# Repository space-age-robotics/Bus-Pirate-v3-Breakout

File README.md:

Bus-Pirate-v3-Breakout
======================

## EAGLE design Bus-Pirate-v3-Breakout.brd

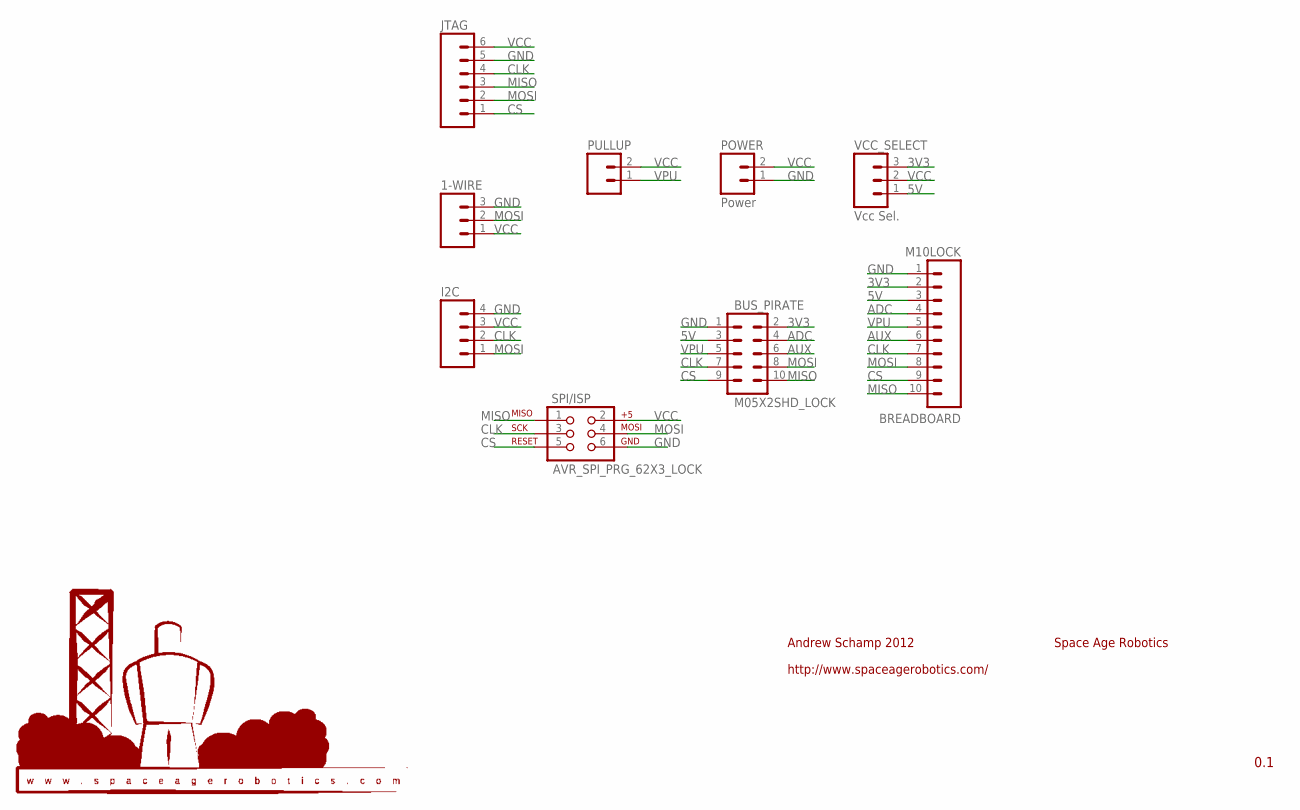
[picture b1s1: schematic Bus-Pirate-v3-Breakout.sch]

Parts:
1-WIRE: M03LOCK; 1X03_LOCK
BREADBOARD: M10LOCK; 1X10_LOCK
BUS_PIRATE: M05X2SHD_LOCK; 2X5-LOCK
I2C: M04LOCK; 1X04_LOCK
JTAG: M06LOCK; 1X06_LOCK
POWER: Power; 1X02_LOCK
PULLUP: M02LOCK; 1X02_LOCK
SPI/ISP: AVR_SPI_PRG_62X3_LOCK; 2X3_LOCK
U$2: LOGO_SPACE_AGE_ROBOTICS0.48*0.27; LOGO_SPACE_AGE_ROBOTICS_SMALL_0.48X0.27
VCC_SELECT: Vcc Sel.; 1X03_LOCK

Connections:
3V3: BREADBOARD.2, BUS_PIRATE.2, VCC_SELECT.3
5V: BREADBOARD.3, BUS_PIRATE.3, VCC_SELECT.1
ADC: BREADBOARD.4, BUS_PIRATE.4
AUX: BREADBOARD.6, BUS_PIRATE.6
CLK: BREADBOARD.7, BUS_PIRATE.7, I2C.2, JTAG.4, SPI/ISP.3
CS: BREADBOARD.9, BUS_PIRATE.9, JTAG.1, SPI/ISP.5
GND: 1-WIRE.3, BREADBOARD.1, BUS_PIRATE.1, I2C.4, JTAG.5, POWER.1, SPI/ISP.6
MISO: BREADBOARD.10, BUS_PIRATE.10, JTAG.3, SPI/ISP.1
MOSI: 1-WIRE.2, BREADBOARD.8, BUS_PIRATE.8, I2C.1, JTAG.2, SPI/ISP.4
VCC: 1-WIRE.1, I2C.3, JTAG.6, POWER.2, PULLUP.2, SPI/ISP.2, VCC_SELECT.2
VPU: BREADBOARD.5, BUS_PIRATE.5, PULLUP.1

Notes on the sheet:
0.1
Andrew Schamp 2012
http://www.spaceagerobotics.com/
Space Age Robotics

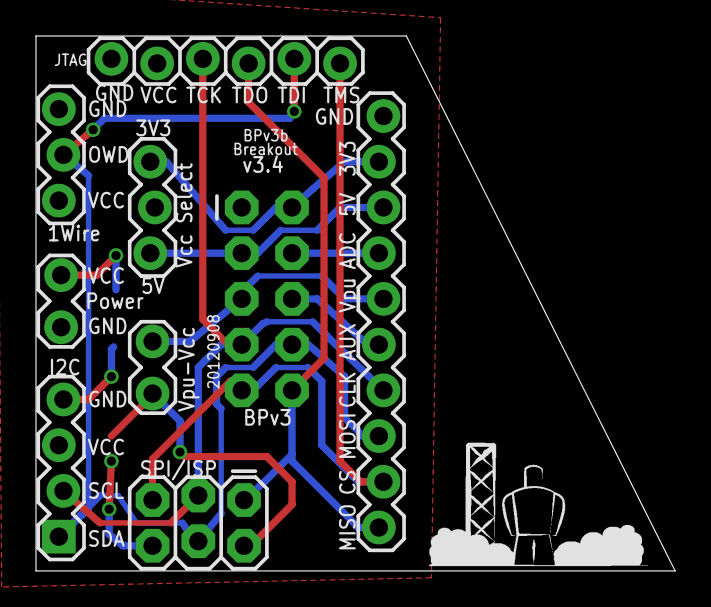
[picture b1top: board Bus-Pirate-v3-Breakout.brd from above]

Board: 2 copper layers, 35.5 x 29.7 mm, 10 parts (0 on the bottom side), 11 nets.

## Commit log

2012-09-06 Initial migration from old repo
2012-09-07 First cut of refactor to add JTAG
2012-09-10 Clean up and add panelization config

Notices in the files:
parts and their libraries:
SparkFun-Connectors: Licensing: CC v3.0 Share-Alike You are welcome to use this library for commercial purposes.
